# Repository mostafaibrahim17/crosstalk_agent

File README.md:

# Explainable Crosstalk Diagnosis on Arango

> A signal-integrity agent that finds the physical adjacency behind a board defect, ranks it,
> and cites how it was fixed before, as one query over one multimodel store.

<p align="center">
  <em>A board defect is not a value in one table. It is a relationship between two nets.</em>
</p>

When a data lane shows frequency variation and a rising bit error rate, every trace passes its
own design-rule check and the board still fails. The fault is not in any single net. It is a
**power or clock line running too close to a data line**, over a long enough parallel run to
couple noise into it. That proximity is an **edge, not a row**, which is exactly why
record-by-record inspection misses it.

This build models the board as a graph, gives that graph a memory of past defects, and resolves
both in a single [AQL](https://docs.arango.ai/arangodb/stable/aql/) query on the
[Arango Contextual Data Platform](https://arango.ai/products/contextual-data-platform).

---

## Architecture

One store holds three data shapes, and one query path turns a symptom into an explainable,
cited cause:

- **Design graph** - the KiCad board parsed into nets (nodes) and adjacency edges carrying
  spacing, parallel length, layer, and trace width.
- **Vector store** - past defect reports embedded for similarity recall via `APPROX_NEAR_COSINE`.
- **Knowledge graph** - built by [AutoGraph](https://docs.arango.ai/agentic-ai-suite/autograph/)
  from the same corpus, cited through the
  [GraphRAG Retriever](https://docs.arango.ai/agentic-ai-suite/graphrag/).

The agent recalls similar defects, traverses to the physical neighbors, **scores** each
candidate, **judges** which one explains the symptom, and returns a **cited fix**. The graph
proves the geometry; the agent interprets the cause.

---

## The hero fault

Point the engine at a real Raspberry Pi CM4 IO board with `python src/agent.py auto`. It scans
every adjacency, scores each one, and diagnoses the worst, with no victim hardcoded:

```
=== VICTIM ===
DSI1_D0_N (net_47)  symptom: frequency variation and rising bit error rate

=== CANDIDATES (ranked, proved) ===
  DSI0_C_P   sev 0.5873  [leading]    clock   gap 0.42mm  len 43.3mm  B.Cu
  DSI0_C_N   sev 0.4487  [unlikely]   clock   gap 0.80mm  len 43.3mm  B.Cu

=== RECALLED CASES ===
  Frequency variation traced to an impedance mismatch      <- same symptom, wrong cause
  Camera lane jitter from an adjacent high-speed signal
  Clock-to-data coupling over a long adjacent run

=== JUDGE (interpretation, a hypothesis) ===
  chosen: DSI0_C_P
  judge confidence: medium  ->  finding tier [corroborated]
  reasoning: DSI0_C_P runs on the same outer copper for 43.3 mm at 0.42 mm, a clock
  whose fast edges couple into a neighbouring data lane, matching the symptom.

=== CITED FIX (retriever) ===
  Increase local spacing; add a grounded guard trace with stitching vias; or reroute
  the aggressor to an inner layer. [cites the clock-coupling reports]

=== CORROBORATION ===
  mechanism converged : True
  verdict             : AGREE - graph and citation point at the same story
```

A DSI clock lane running 43 mm alongside a data lane from a *different* camera interface, 0.42 mm
apart on the bottom layer. The top vector match ("impedance mismatch") is the **wrong** cause,
sharing the symptom but not the geometry, and the graph corrects it.

---

## Why this architecture

The finding rests on **two independent surfaces agreeing**. The graph-and-judge chose the clock
coupling from geometry and reasoning. The Retriever, reading only the chosen cause, cited past
reports about the same mechanism from the knowledge graph. Neither was told the other's answer,
and they converged.

That convergence is the payoff of one multimodel store. A split stack, a graph database beside
a vector database, runs two queries, holds partial results in application code, and rebuilds the
join that finds the fault on every request. A vector-only tool has no topology to traverse and
cannot tell a real adjacency from a look-alike report. Two different shapes of the same store,
reaching the same mechanism independently, is the confidence a fragmented stack has no way to
reach.

The severity score weighs spacing and parallel length equally, because crosstalk accumulates
along a coupled run. The hero scores **high on length and loudness, low on spacing**, the exact
profile a proximity-only check misses.

---

## Quickstart

```bash
# clone and enter
git clone <your-repo-url> crosstalk-agent
cd crosstalk-agent

# virtual environment
python -m venv venv
source venv/bin/activate            # Windows: venv\Scripts\activate

# dependencies
pip install -r requirements.txt

# credentials
cp .env.example .env                # then edit with your details
```

```
# .env
ARANGO_HOST=https://<your-deployment>.arangodb.cloud
ARANGO_DB=crosstalk_v1
ARANGO_USER=root
ARANGO_PASSWORD=<your-password>
OPENAI_API_KEY=<your-key>
RETRIEVER_ID=                       # set after deploying the Retriever
RETRIEVER_BASE=
```

Build the data and run the diagnosis:

```bash
python src/prepare_autograph.py     # 1. write the synthetic defect corpus (30 reports)
python src/ingest.py                # 2. parse the board, load graph + vectors + index
python src/agent.py auto            # 3. scan the board, diagnose the worst adjacency
python src/agent.py auto --deep     # 3b. same, with Deep Search for a fuller cited playbook
```

**Step 2** reports `{'nets': 73, 'adjacencies': 10, 'defect_reports': 30, 'dimension': 1536}`.
Of 75 candidate net pairs, 65 are intended routing (differential pairs and same-interface buses)
and are skipped; the 10 that remain are the real cross-interface adjacencies.

To enable cited fixes, upload `data/autograph/*.md` to **AutoGraph Studio** in the Arango web
interface, build the graph with `text-embedding-3-small`, deploy the Retriever, and set
`RETRIEVER_ID` / `RETRIEVER_BASE`. The step-by-step walkthrough is in
[docs/setting-up-autograph-and-the-retriever.md](docs/setting-up-autograph-and-the-retriever.md).
Without it, the agent falls back to a local corpus citation and the rest of the pipeline runs
unchanged.

---

## The notebook

`crosstalk_analysis.ipynb` runs the whole pipeline end to end, cell by cell, from a fresh
database to the final figures. It closes with five visuals, all saved to `assets/`:

| figure | what it shows |
|---|---|
|  | every real adjacency, colored by class, sized by severity |
|  | the ten adjacencies ranked; the hero clears the field |
|  | spacing / length / loudness per candidate |
|  | spacing vs parallel length, with the 3W danger line |

---

## Repository layout

```
src/
  config.py             every knob: net classes, the 3W rule, severity weights, tiers
  parse_board.py        KiCad board -> nets and adjacency edges (skips intended routing)
  ingest.py             load the graph, embed the corpus, build the vector index
  prepare_autograph.py  generate the synthetic defect corpus for AutoGraph
  agent.py              the resolver: recall, traverse, score, judge, cite, corroborate
  agent_graph.py        the same investigation, driven by a LangGraph ReAct agent
data/
  CM4IOUSB3.kicad_pcb   the board
  autograph/            the generated corpus (markdown + manifest.json)
docs/
  setting-up-autograph-and-the-retriever.md   AutoGraph + Retriever provisioning walkthrough
assets/                 architecture diagram + figures saved by the notebook
crosstalk_analysis.ipynb
```

Every knob the engine turns lives in `config.py`. Swap your own process design kit's spacing
rule into the 3W threshold, point the parser at your board, and the ranking retunes with no
edit to any query.

---

## Two agents, one engine

The resolver in `agent.py` decides the step order itself. `agent_graph.py` hands the same three
tools (`traverse_and_score`, `recall_similar`, `cite_fix`) to a LangGraph ReAct agent that
chooses the order. Same tools, same database, same answer: the engine is the data and the query,
not the orchestration around it.

---

## Honest edges

The engine only catches faults that can be modeled as a relationship between nets; a defect that
is not an adjacency is invisible to it. The adjacency edges depend on a proximity threshold
someone chose. The top cause is a lead, not a verdict, capped at `corroborated` until confirmed
on silicon. The board is real geometry; the defect corpus is synthetic and labeled as such, so
the build demonstrates the method rather than real hardware history.

The same traversal extends to impedance mismatch, return-path discontinuity, and power-integrity
issues, because each is a relationship in the same graph. Run it earlier and it becomes a
design-rule check: the parser reads a layout in progress and flags an adjacency the day it is
routed, before any board is fabricated.

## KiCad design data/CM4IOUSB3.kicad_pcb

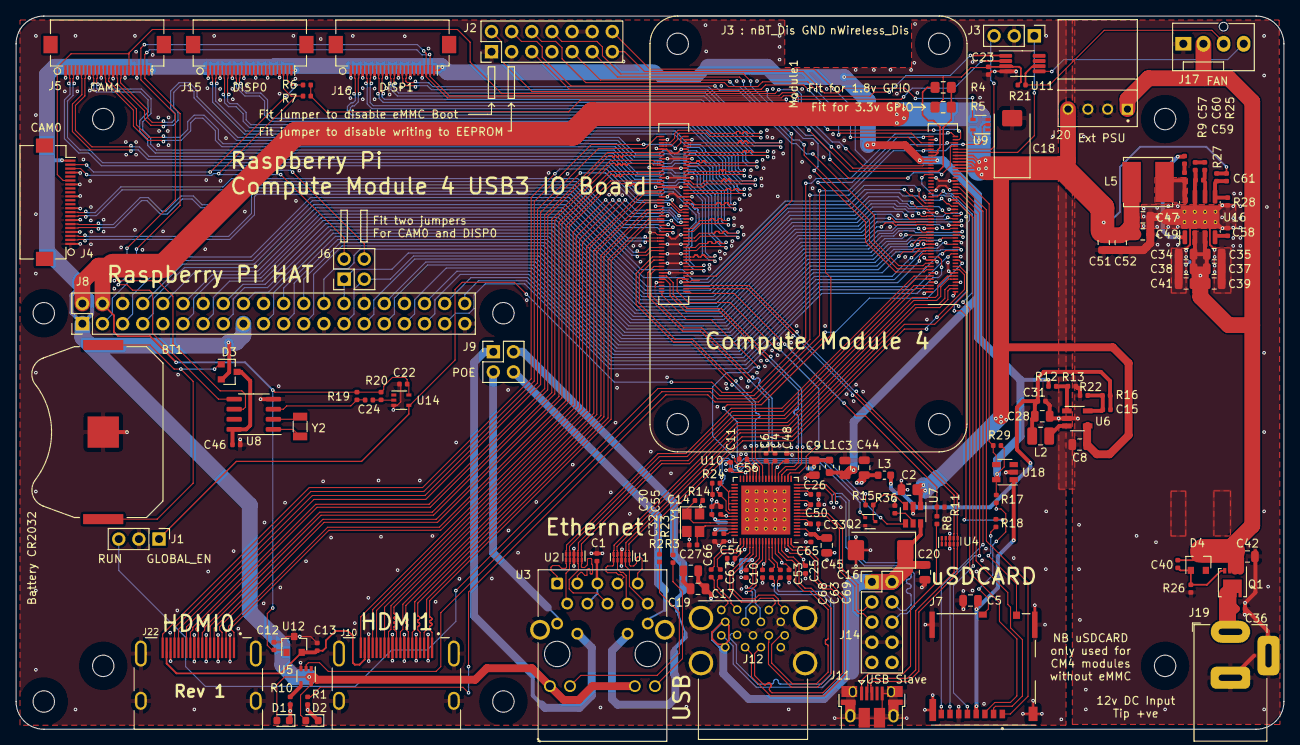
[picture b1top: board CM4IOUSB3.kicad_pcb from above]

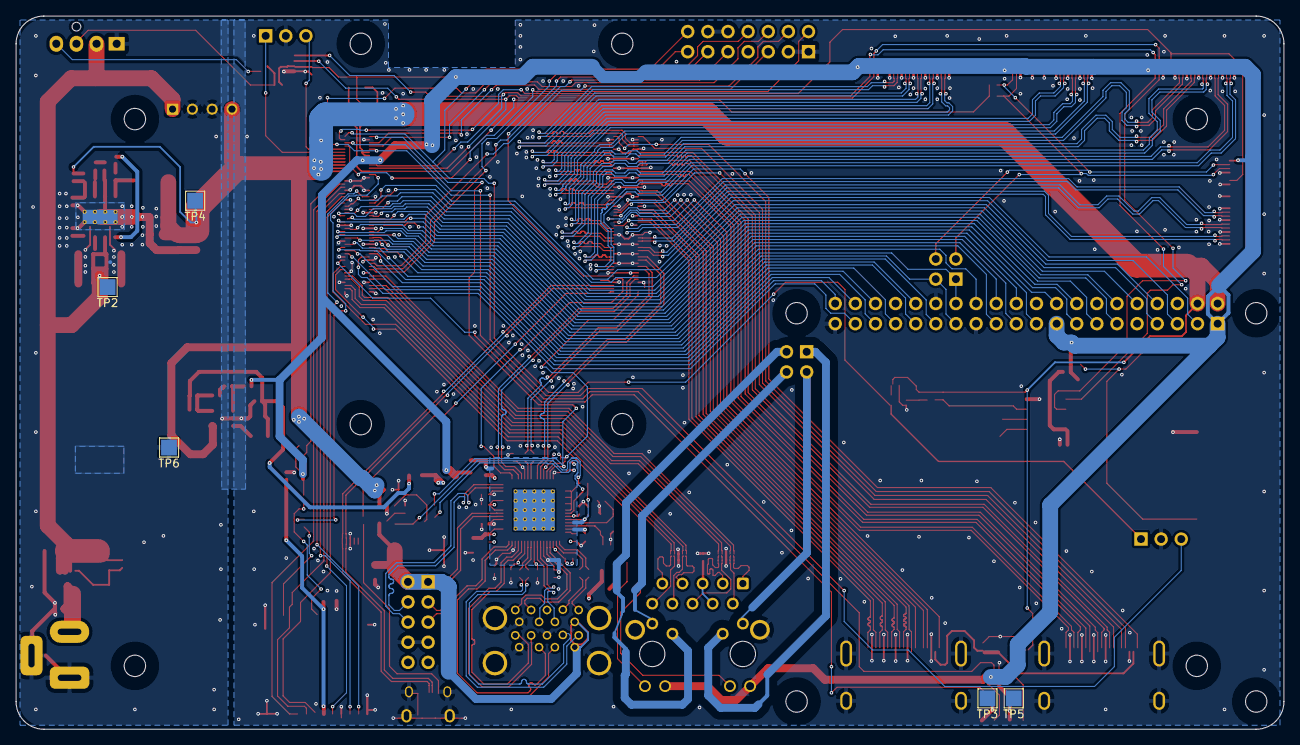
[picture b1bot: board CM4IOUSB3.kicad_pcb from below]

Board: 4 copper layers, 160.0 x 90.0 mm, 154 parts (5 on the bottom side), 209 nets.

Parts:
BT1: Battery_Cell; BatteryHolder_Keystone_3034_1x20mm
C1, C4, C6, C10, C11, C12, C13, C22, C23, C24, C25, C26, C30, C31, C32, C33, C40, C46, C48, C50, C53, C54, C55, C56, C57, C58, C63, C65, C66, C67, C68, C69: 100n; C_0402_1005Metric
C2, C3, C5, C8, C9, C17, C19, C20, C28, C44, C45, C47, C49, C51, C52: 10u; C_0805_2012Metric
C14, C15, C27: 22pF; C_0402_1005Metric
C16, C18: 100uF; CP_EIA-7343-31_Kemet-D
C34, C35, C37, C38, C39, C41, C42: 10u 35v; C_0805_2012Metric
C36: 100n 100v; C_0402_1005Metric
C59, C61: nf; C_0402_1005Metric
C60: 1.2nF; C_0402_1005Metric
D1: LED Red; LED_0603_1608Metric
D2: LED Green; LED_0603_1608Metric
D3: BAT54C-7-F; SOT-23
D4: MMBZ5242BLT3G; D_SOT-23_ANK
H1, H2, H3, H4, H5, H6, H7, H8: MountingHole; MountingHole_2.7mm_M2.5
J1, J3: Conn_01x03; PinHeader_1x03_P2.54mm_Vertical
J2: Conn_02x07_Odd_Even; PinHeader_2x07_P2.54mm_Vertical
J4, J5, J15, J16: Conn_01x22_Female; Hirose_FH12-22S-0.5SH_1x22-1MP_P0.50mm_Horizontal
J6, J9: THD-02-R; PinHeader_2x02_P2.54mm_Vertical
J7: Micro_SD_Card_Det; SDCARD_MOLEX_503398-1892
J8: THD-20-R; PinHeader_2x20_P2.54mm_Vertical
J10, J22: 690-019-298-412; EDAC 690-019-298-412
J11: USB_OTG; USB_Micro-B_EDAC_UCON00686
J12: USB3_A; MTCONN_UBAF30-D2011
J14: Conn_02x05_Odd_Even; PinHeader_2x05_P2.54mm_Vertical
J17: Molex 470531000; FanPinHeader_1x04_P2.54mm_Vertical
J19: Barrel_Jack; BarrelJack_Horizontal
J20: AMP171826-4; TE_171826-4
L1, L3: BLM18AG221SN1; L_0603_1608Metric
L2: 2.2uH; L_1008_2520Metric
L5: SRN6045TA-3R3Y; L_Bourns_SRN6045TA
Module1: ComputeModule4; Raspberry-Pi-4-Compute-Module
Q1: DMP3013SFV-7; Diodes_PowerDI3333-8
Q2: DMG1012T; SOT-523
R1, R10: 1k; R_0402_1005Metric
R2, R3: 470R; R_0402_1005Metric
R4: nf; R_0805_2012Metric_Pad1.15x1.40mm_HandSolder
R5: 0R; R_0805_2012Metric_Pad1.15x1.40mm_HandSolder
R6, R7, R8, R11, R28: 2.2K 1%; R_0402_1005Metric
R9: 10R; R_0402_1005Metric
R12, R13, R14, R15, R24, R36: 15K 1%; R_0402_1005Metric
R16, R26, R27, R29: 12K 1%; R_0402_1005Metric
R17, R18: nf; R_0402_1005Metric
R19, R20: 510K 1%; R_0402_1005Metric
R21: 36K 1%; R_0402_1005Metric
R22: 16K; R_0402_1005Metric
R23: 6.04K; R_0402_1005Metric
R25: 20K 1%; R_0402_1005Metric
TP2, TP3, TP4, TP5, TP6: TestPoint; TestPoint_Pad_2.0x2.0mm
U1, U2, U4: TPD4EUSB30; USON-10_2.5x1.0mm_P0.5mm
U3: MagJack-A70-112-331N126; TRJG0926HENL
U5, U9, U14: 74LVC1G07SE-7; SOT-353_SC-70-5
U6: AP3429KTTR-G1; TSOT-23-5
U7: AP22653W6; SOT-23-6
U8: PCF85063AT/AAZ; SOIC-8_3.9x4.9mm_P1.27mm
U10: VL805; QFN-68-1EP_8x8mm_P0.4mm_EP5.2x5.2mm_ThermalVias
U11: EMC2301-1-ACZL-TR; MSOP-8_3x3mm_P0.65mm
U12: RT9742SNGV; SOT-23
U16: AP64501SP-13; SOIC-8-1EP_3.9x4.9mm_P1.27mm_EP2.95x4.9mm_Mask2.71x3.4mm_Th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
U18: RT9742GGJ5; SOT-23-5
Y1: 25MHz; Crystal_SMD_SeikoEpson_FA238-4Pin_3.2x2.5mm
Y2: X32K768S301; Crystal_SMD_3215-2Pin_3.2x1.5mm

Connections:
/+3.3v: C3.1, C23.1, D1.2 (A), D2.2 (A), D3.2, J4.22, J5.22, J8.1, J8.17, J15.22, J16.22, L1.1, Module1.84 (+3.3v_(Output)), Module1.86 (+3.3v_(Output)), R5.1, R12.1, R17.1, R21.2, R29.1, U3.15 (LEDG_A), U3.17 (LEDY_A), U5.5 (VCC), U11.3 (VDD), U18.5 (IN)
/+5v: C2.1, C8.1, C12.1, C18.1, C22.1, C47.1, C49.1, C51.1, C52.1, C61.1, J8.2, J8.4, J20.4, L5.2, Module1.77 (+5v_(Input)), Module1.79 (+5v_(Input)), Module1.81 (+5v_(Input)), Module1.83 (+5v_(Input)), Module1.85 (+5v_(Input)), Module1.87 (+5v_(Input)), R19.2, R20.2, R27.1, TP4.1, U6.4 (VIN), U7.1 (IN), U9.5 (VCC), U12.1 (IN), U14.5 (VCC)
/+12v: C34.1, C35.1, C37.1, C38.1, C39.1, C40.1, C41.1, C42.1, D4.1 (K), J17.2, J20.1, Q1.1 (S), Q1.2 (S), Q1.3 (S), TP2.1, U16.2 (VIN), U16.3 (EN)
/CM4_GPIO ( Ethernet, GPIO, SDCARD)/+1.8v: Module1.88 (+1.8v_(Output)), Module1.90 (+1.8v_(Output)), R4.1
/CM4_GPIO ( Ethernet, GPIO, SDCARD)/AIN0: J2.5, Module1.96 (AnalogIP0)
/CM4_GPIO ( Ethernet, GPIO, SDCARD)/AIN1: J2.6, Module1.94 (AnalogIP1)
/CM4_GPIO ( Ethernet, GPIO, SDCARD)/BT_nDis: J3.3, Module1.91 (BT_nDisable)
/CM4_GPIO ( Ethernet, GPIO, SDCARD)/EEPROM_nWP: J2.4, Module1.20 (EEPROM_nWP)
/CM4_GPIO ( Ethernet, GPIO, SDCARD)/ETH_LEDG: Module1.17 (Ethernet_nLED2(3.3v)), R2.2
/CM4_GPIO ( Ethernet, GPIO, SDCARD)/ETH_LEDY: Module1.15 (Ethernet_nLED3(3.3v)), R3.2
/CM4_GPIO ( Ethernet, GPIO, SDCARD)/GLOBAL_EN: J1.1, J2.14, Module1.99 (Global_EN), U14.4
/CM4_GPIO ( Ethernet, GPIO, SDCARD)/GPIO2: J8.3, Module1.58 (GPIO2)
/CM4_GPIO ( Ethernet, GPIO, SDCARD)/GPIO3: J8.5, Module1.56 (GPIO3)
/CM4_GPIO ( Ethernet, GPIO, SDCARD)/GPIO4: J8.7, Module1.54 (GPIO4)
/CM4_GPIO ( Ethernet, GPIO, SDCARD)/GPIO5: J8.29, Module1.34 (GPIO5)
/CM4_GPIO ( Ethernet, GPIO, SDCARD)/GPIO6: J8.31, Module1.30 (GPIO6)
/CM4_GPIO ( Ethernet, GPIO, SDCARD)/GPIO7: J8.26, Module1.37 (GPIO7)
/CM4_GPIO ( Ethernet, GPIO, SDCARD)/GPIO8: J8.24, Module1.39 (GPIO8)
/CM4_GPIO ( Ethernet, GPIO, SDCARD)/GPIO9: J8.21, Module1.40 (GPIO9)
/CM4_GPIO ( Ethernet, GPIO, SDCARD)/GPIO10: J8.19, Module1.44 (GPIO10)
/CM4_GPIO ( Ethernet, GPIO, SDCARD)/GPIO11: J8.23, Module1.38 (GPIO11)
/CM4_GPIO ( Ethernet, GPIO, SDCARD)/GPIO12: J8.32, Module1.31 (GPIO12)
/CM4_GPIO ( Ethernet, GPIO, SDCARD)/GPIO13: J8.33, Module1.28 (GPIO13)
/CM4_GPIO ( Ethernet, GPIO, SDCARD)/GPIO14: J8.8, Module1.55 (GPIO14)
/CM4_GPIO ( Ethernet, GPIO, SDCARD)/GPIO15: J8.10, Module1.51 (GPIO15)
/CM4_GPIO ( Ethernet, GPIO, SDCARD)/GPIO16: J8.36, Module1.29 (GPIO16)
/CM4_GPIO ( Ethernet, GPIO, SDCARD)/GPIO17: J8.11, Module1.50 (GPIO17)
/CM4_GPIO ( Ethernet, GPIO, SDCARD)/GPIO18: J8.12, Module1.49 (GPIO18)
/CM4_GPIO ( Ethernet, GPIO, SDCARD)/GPIO19: J8.35, Module1.26 (GPIO19)
/CM4_GPIO ( Ethernet, GPIO, SDCARD)/GPIO20: J8.38, Module1.27 (GPIO20)
/CM4_GPIO ( Ethernet, GPIO, SDCARD)/GPIO21: J8.40, Module1.25 (GPIO21)
/CM4_GPIO ( Ethernet, GPIO, SDCARD)/GPIO22: J8.15, Module1.46 (GPIO22)
/CM4_GPIO ( Ethernet, GPIO, SDCARD)/GPIO23: J8.16, Module1.47 (GPIO23)
/CM4_GPIO ( Ethernet, GPIO, SDCARD)/GPIO24: J8.18, Module1.45 (GPIO24)
/CM4_GPIO ( Ethernet, GPIO, SDCARD)/GPIO25: J8.22, Module1.41 (GPIO25)
/CM4_GPIO ( Ethernet, GPIO, SDCARD)/GPIO26: J8.37, Module1.24 (GPIO26)
/CM4_GPIO ( Ethernet, GPIO, SDCARD)/GPIO27: J8.13, Module1.48 (GPIO27)
/CM4_GPIO ( Ethernet, GPIO, SDCARD)/GPIO_VREF: Module1.78 (GPIO_VREF(1.8v/3.3v_Input)), R4.2, R5.2, R6.1, R7.1
/CM4_GPIO ( Ethernet, GPIO, SDCARD)/ID_SC: J6.1, J8.28, Module1.35 (ID_SC)
/CM4_GPIO ( Ethernet, GPIO, SDCARD)/ID_SD: J6.3, J8.27, Module1.36 (ID_SD)
/CM4_GPIO ( Ethernet, GPIO, SDCARD)/RUN_PG: J1.3, Module1.92 (RUN_PG), U9.2
/CM4_GPIO ( Ethernet, GPIO, SDCARD)/Reserved: Module1.76 (Reserved), R18.1
/CM4_GPIO ( Ethernet, GPIO, SDCARD)/SD_CLK: J7.5 (CLK), Module1.57 (SD_CLK)
/CM4_GPIO ( Ethernet, GPIO, SDCARD)/SD_CMD: J7.3 (CMD), Module1.62 (SD_CMD)
/CM4_GPIO ( Ethernet, GPIO, SDCARD)/SD_DAT0: J7.7 (DAT0), Module1.63 (SD_DAT0)
/CM4_GPIO ( Ethernet, GPIO, SDCARD)/SD_DAT1: J7.8 (DAT1), Module1.67 (SD_DAT1)
/CM4_GPIO ( Ethernet, GPIO, SDCARD)/SD_DAT2: J7.1 (DAT2), Module1.69 (SD_DAT2)
/CM4_GPIO ( Ethernet, GPIO, SDCARD)/SD_DAT3: J7.2 (DAT3/CD), Module1.61 (SD_DAT3)
/CM4_GPIO ( Ethernet, GPIO, SDCARD)/SD_PWR: C5.1, J7.4 (VDD), U18.1 (OUT)
/CM4_GPIO ( Ethernet, GPIO, SDCARD)/SD_PWR_ON: Module1.75 (SD_PWR_ON), R29.2, U18.4 (EN)
/CM4_GPIO ( Ethernet, GPIO, SDCARD)/SYNC_IN: J2.8, Module1.16 (Ethernet_SYNC_IN(1.8v))
/CM4_GPIO ( Ethernet, GPIO, SDCARD)/SYNC_OUT: J2.9, Module1.18 (Ethernet_SYNC_OUT(1.8v))
/CM4_GPIO ( Ethernet, GPIO, SDCARD)/TR0_TAP: J9.3, U3.11 (VC1)
/CM4_GPIO ( Ethernet, GPIO, SDCARD)/TR1_TAP: J9.1, U3.12 (VC2)
/CM4_GPIO ( Ethernet, GPIO, SDCARD)/TR2_TAP: J9.2, U3.13 (VC3)
/CM4_GPIO ( Ethernet, GPIO, SDCARD)/TR3_TAP: J9.4, U3.14 (VC4)
/CM4_GPIO ( Ethernet, GPIO, SDCARD)/TRD0_N: Module1.10 (Ethernet_Pair0_N), U2.4 (D2+), U2.7, U3.2 (TRD0-)
/CM4_GPIO ( Ethernet, GPIO, SDCARD)/TRD0_P: Module1.12 (Ethernet_Pair0_P), U2.5 (D2-), U2.6, U3.1 (TRD0+)
/CM4_GPIO ( Ethernet, GPIO, SDCARD)/TRD1_N: Module1.6 (Ethernet_Pair1_N), U2.2 (D1-), U2.9, U3.6 (TRD1-)
/CM4_GPIO ( Ethernet, GPIO, SDCARD)/TRD1_P: Module1.4 (Ethernet_Pair1_P), U2.1 (D1+), U2.10, U3.3 (TRD1+)
/CM4_GPIO ( Ethernet, GPIO, SDCARD)/TRD2_N: Module1.9 (Ethernet_Pair2_N), U1.4 (D2+), U1.7, U3.8 (TRD2-)
/CM4_GPIO ( Ethernet, GPIO, SDCARD)/TRD2_P: Module1.11 (Ethernet_Pair2_P), U1.5 (D2-), U1.6, U3.7 (TRD2+)
/CM4_GPIO ( Ethernet, GPIO, SDCARD)/TRD3_N: Module1.5 (Ethernet_Pair3_N), U1.2 (D1-), U1.9, U3.10 (TRD3-)
/CM4_GPIO ( Ethernet, GPIO, SDCARD)/TRD3_P: Module1.3 (Ethernet_Pair3_P), U1.1 (D1+), U1.10, U3.9 (TRD3+)
/CM4_GPIO ( Ethernet, GPIO, SDCARD)/TV_OUT: J2.11, Module1.111 (VDAC_COMP)
/CM4_GPIO ( Ethernet, GPIO, SDCARD)/WL_nDis: J3.1, Module1.89 (WL_nDisable)
/CM4_GPIO ( Ethernet, GPIO, SDCARD)/nPWR_LED: Module1.95 (nPI_LED_PWR), U5.2
/CM4_GPIO ( Ethernet, GPIO, SDCARD)/nRPIBOOT: J2.2, Module1.93 (nRPIBOOT)
/CM4_HighSpeed/CAM0_C_N: J4.8, Module1.140 (CAM0_C_N)
/CM4_HighSpeed/CAM0_C_P: J4.9, Module1.142 (CAM0_C_P)
/CM4_HighSpeed/CAM0_D0_N: J4.2, Module1.128 (CAM0_D0_N)
/CM4_HighSpeed/CAM0_D0_P: J4.3, Module1.130 (CAM0_D0_P)
/CM4_HighSpeed/CAM0_D1_N: J4.5, Module1.134 (CAM0_D1_N)
/CM4_HighSpeed/CAM0_D1_P: J4.6, Module1.136 (CAM0_D1_P)
/CM4_HighSpeed/CAM1_C_N: J5.8, Module1.127 (CAM1_C_N)
/CM4_HighSpeed/CAM1_C_P: J5.9, Module1.129 (CAM1_C_P)
/CM4_HighSpeed/CAM1_D0_N: J5.2, Module1.115 (CAM1_D0_N)
/CM4_HighSpeed/CAM1_D0_P: J5.3, Module1.117 (CAM1_D0_P)
/CM4_HighSpeed/CAM1_D1_N: J5.5, Module1.121 (CAM1_D1_N)
/CM4_HighSpeed/CAM1_D1_P: J5.6, Module1.123 (CAM1_D1_P)
/CM4_HighSpeed/CAM1_D2_N: J5.11, Module1.133 (CAM1_D2_N)
/CM4_HighSpeed/CAM1_D2_P: J5.12, Module1.135 (CAM1_D2_P)
/CM4_HighSpeed/CAM1_D3_N: J5.14, Module1.139 (CAM1_D3_N)
/CM4_HighSpeed/CAM1_D3_P: J5.15, Module1.141 (CAM1_D3_P)
/CM4_HighSpeed/CAM_GPIO: J4.17, J5.17, Module1.97 (Camera_GPIO)
/CM4_HighSpeed/DSI0_C_N: J15.8, Module1.169 (DSI0_C_N)
/CM4_HighSpeed/DSI0_C_P: J15.9, Module1.171 (DSI0_C_P)
/CM4_HighSpeed/DSI0_D0_N: J15.2, Module1.157 (DSI0_D0_N)
/CM4_HighSpeed/DSI0_D0_P: J15.3, Module1.159 (DSI0_D0_P)
/CM4_HighSpeed/DSI0_D1_N: J15.5, Module1.163 (DSI0_D1_N)
/CM4_HighSpeed/DSI0_D1_P: J15.6, Module1.165 (DSI0_D1_P)
/CM4_HighSpeed/DSI1_C_N: J16.8, Module1.187 (DSI1_C_N)
/CM4_HighSpeed/DSI1_C_P: J16.9, Module1.189 (DSI1_C_P)
/CM4_HighSpeed/DSI1_D0_N: J16.2, Module1.175 (DSI1_D0_N)
/CM4_HighSpeed/DSI1_D0_P: J16.3, Module1.177 (DSI1_D0_P)
/CM4_HighSpeed/DSI1_D1_N: J16.5, Module1.181 (DSI1_D1_N)
/CM4_HighSpeed/DSI1_D1_P: J16.6, Module1.183 (DSI1_D1_P)
/CM4_HighSpeed/DSI1_D2_N: J16.11, Module1.193 (DSI1_D2_N)
/CM4_HighSpeed/DSI1_D2_P: J16.12, Module1.195 (DSI1_D2_P)
/CM4_HighSpeed/DSI1_D3_N: J16.14, Module1.194 (DSI1_D3_N)
/CM4_HighSpeed/DSI1_D3_P: J16.15, Module1.196 (DSI1_D3_P)
/CM4_HighSpeed/HDMI0_CEC: J22.13 (CEC), Module1.151 (HDMI0_CEC)
/CM4_HighSpeed/HDMI0_CK_N: J22.12 (CK-), Module1.190 (HDMI0_CLK_N)
/CM4_HighSpeed/HDMI0_CK_P: J22.10 (CK+), Module1.188 (HDMI0_CLK_P)
/CM4_HighSpeed/HDMI0_D0_N: J22.9 (D0-), Module1.184 (HDMI0_TX0_N)
/CM4_HighSpeed/HDMI0_D0_P: J22.7 (D0+), Module1.182 (HDMI0_TX0_P)
/CM4_HighSpeed/HDMI0_D1_N: J22.6 (D1-), Module1.178 (HDMI0_TX1_N)
/CM4_HighSpeed/HDMI0_D1_P: J22.4 (D1+), Module1.176 (HDMI0_TX1_P)
/CM4_HighSpeed/HDMI0_D2_N: J22.3 (D2-), Module1.172 (HDMI0_TX2_N)
/CM4_HighSpeed/HDMI0_D2_P: J22.1 (D2+), Module1.170 (HDMI0_TX2_P)
/CM4_HighSpeed/HDMI0_HOTPLUG: J22.19 (HPD/HEAC-), Module1.153 (HDMI0_HOTPLUG)
/CM4_HighSpeed/HDMI0_SCL: J22.15 (SCL), Module1.200 (HDMI0_SCL)
/CM4_HighSpeed/HDMI0_SDA: J22.16 (SDA), Module1.199 (HDMI0_SDA)
/CM4_HighSpeed/HDMI1_CEC: J10.13 (CEC), Module1.149 (HDMI1_CEC)
/CM4_HighSpeed/HDMI1_CK_N: J10.12 (CK-), Module1.166 (HDMI1_CLK_N)
/CM4_HighSpeed/HDMI1_CK_P: J10.10 (CK+), Module1.164 (HDMI1_CLK_P)
/CM4_HighSpeed/HDMI1_D0_N: J10.9 (D0-), Module1.160 (HDMI1_TX0_N)
/CM4_HighSpeed/HDMI1_D0_P: J10.7 (D0+), Module1.158 (HDMI1_TX0_P)
/CM4_HighSpeed/HDMI1_D1_N: J10.6 (D1-), Module1.154 (HDMI1_TX1_N)
/CM4_HighSpeed/HDMI1_D1_P: J10.4 (D1+), Module1.152 (HDMI1_TX1_P)
/CM4_HighSpeed/HDMI1_D2_N: J10.3 (D2-), Module1.148 (HDMI1_TX2_N)
/CM4_HighSpeed/HDMI1_D2_P: J10.1 (D2+), Module1.146 (HDMI1_TX2_P)
/CM4_HighSpeed/HDMI1_HOTPLUG: J10.19 (HPD/HEAC-), Module1.143 (HDMI1_HOTPLUG)
/CM4_HighSpeed/HDMI1_SCL: J10.15 (SCL), Module1.147 (HDMI1_SCL)
/CM4_HighSpeed/HDMI1_SDA: J10.16 (SDA), Module1.145 (HDMI1_SDA)
/CM4_HighSpeed/HDMI_5v: C13.1, J10.18 (+5V), J22.18 (+5V), U12.2 (OUT)
/CM4_HighSpeed/PCIE_CLK_N: Module1.112 (PCIe_CLK_N), U10.21 (PEXCLK_P)
/CM4_HighSpeed/PCIE_CLK_P: Module1.110 (PCIe_CLK_P), U10.22 (PEXCLK_N)
/CM4_HighSpeed/PCIE_CLK_nREQ: Module1.102 (PCIe_CLK_nREQ), U10.30 (nPEXCLKREQ)
/CM4_HighSpeed/PCIE_RX_N: C6.2, Module1.118 (PCIe_RX_N)
/CM4_HighSpeed/PCIE_RX_P: C4.2, Module1.116 (PCIe_RX_P)
/CM4_HighSpeed/PCIE_TX_N: Module1.124 (PCIe_TX_N), U10.28 (PEXRX_N)
/CM4_HighSpeed/PCIE_TX_P: Module1.122 (PCIe_TX_P), U10.27 (PEXRX_P)
/CM4_HighSpeed/PCIE_nRST: Module1.109 (PCIe_nRST), U10.19 (nPEXRST)
/CM4_HighSpeed/SCL0: J5.20, J16.20, Module1.80 (SCL0), U8.6 (SCL), U11.2 (SCL)
/CM4_HighSpeed/SCL1: J4.20, J6.2, J15.20, R7.2
/CM4_HighSpeed/SDA0: J5.21, J16.21, Module1.82 (SDA0), U8.5 (SDA), U11.1 (SDA)
/CM4_HighSpeed/SDA1: J4.21, J6.4, J15.21, R6.2
/CM4_HighSpeed/USBOTG_ID: Module1.101 (USB_OTG_ID), R8.2, R11.1
/RTC , Wakeup, FAN/nRTC_INT: C24.2, R19.1, U8.3 (~INT)
/USB2/USBD_N: J11.2 (D-), Module1.103 (USB2_N), U4.4 (D2+), U4.7
/USB2/USBD_P: J11.3 (D+), Module1.105 (USB2_P), U4.5 (D2-), U4.6
/nEXTRST: Module1.100 (nEXTRST), R15.1, U10.31 (nPONRST)
/xHCI-USB3/A1.05v: C44.1, C45.1, C50.1, C53.1, C54.1, C55.1, C56.1, C63.1, C65.1, L3.2, U10.3 (VCCA10SSRX34), U10.9 (VDD), U10.12 (VCCA10SSRX34), U10.29 (VDD), U10.45 (VDD), U10.54 (VCCA10SSRX12), U10.60 (VDD), U10.63 (VCCA10SSRX12)
/xHCI-USB3/A3.3v: C9.1, C10.1, C11.1, C25.1, C26.1, C30.1, C32.1, C33.1, C48.1, L1.2, R14.1, R24.1, U10.6 (VCCA33SS34), U10.15 (VCCA33SS34), U10.23 (VCCA33PEX), U10.32 (VSUS33), U10.46 (VSUS33), U10.49 (VCCA33SSM), U10.57 (VCCA33SS12), U10.66 (VCCA33SS12)
/xHCI-USB3/C1_N: C67.2, U10.53 (SSTX1_N)
/xHCI-USB3/C1_P: C66.2, U10.52 (SSTX1_P)
/xHCI-USB3/C2_N: C69.2, U10.62 (SSTX2_N)
/xHCI-USB3/C2_P: C68.2, U10.61 (SSTX2_P)
/xHCI-USB3/PD1_N: J12.B2 (D-), U10.59 (USB2D1_N)
/xHCI-USB3/PD1_P: J12.B3 (D+), U10.58 (USB2D1_P)
/xHCI-USB3/PD2_N: J12.A2 (D-), U10.68 (USB2D2_N)
/xHCI-USB3/PD2_P: J12.A3 (D+), U10.67 (USB2D2_P)
/xHCI-USB3/PD3_N: J14.3, U10.8 (USB2D3_N)
/xHCI-USB3/PD3_P: J14.5, U10.7 (USB2D3_P)
/xHCI-USB3/PD4_N: J14.4, U10.17 (USB2D4_N)
/xHCI-USB3/PD4_P: J14.6, U10.16 (USB2D4_P)
/xHCI-USB3/PEXTX_N: C6.1, U10.25 (PEXTX_N)
/xHCI-USB3/PEXTX_P: C4.1, U10.24 (PEXTX_P)
/xHCI-USB3/PWR: Q2.3 (D), R15.2, U7.3 (EN)
/xHCI-USB3/SSRX1_N: J12.B5 (SSRX-), U10.56 (SSRX1_N)
/xHCI-USB3/SSRX1_P: J12.B6 (SSRX+), U10.55 (SSRX1_P)
/xHCI-USB3/SSRX2_N: J12.A6 (SSRX+), U10.65 (SSRX2_N)
/xHCI-USB3/SSRX2_P: J12.A5 (SSRX-), U10.64 (SSRX2_P)
/xHCI-USB3/SSTX1_N: C67.1, J12.B8 (SSTX-)
/xHCI-USB3/SSTX1_P: C66.1, J12.B9 (SSTX+)
/xHCI-USB3/SSTX2_N: C69.1, J12.A9 (SSTX+)
/xHCI-USB3/SSTX2_P: C68.1, J12.A8 (SSTX-)
/xHCI-USB3/VBUS: C16.1, C17.1, C19.1, C20.1, J12.A1 (VBUS), J12.B1 (VBUS), J14.1, J14.2, U7.6 (OUT)
/xHCI-USB3/nOCS1: R24.2, U7.4 (nFault), U10.37 (nUSBHOC4), U10.39 (nUSBHOC3), U10.41 (nUSBHOC2), U10.43 (nUSBHOC1)
/xHCI-USB3/nPWR: Q2.1 (G), R14.2, U10.44 (nUSBHPE1)
GND: BT1.2 (-), C1.2, C2.2, C3.2, C5.2, C8.2, C9.2, C10.2, C11.2, C12.2, C13.2, C14.2, C16.2, C17.2, C18.2, C19.2, C20.2, C22.2, C23.2, C25.2, C26.2, C27.2, C28.2, C30.2, C31.2, C32.2, C33.2, C34.2, C35.2, C36.2, C37.2, C38.2, C39.2, C41.2, C42.2, C44.2, C45.2, C46.2, C47.2, C48.2, C49.2, C50.2, C51.2, C52.2, C53.2, C54.2, C55.2, C56.2, C58.2, C59.2, C60.2, C63.2, C65.2, J1.2, J2.1, J2.3, J2.7, J2.10, J2.12, J3.2, J4.1, J4.4, J4.7, J4.10, J4.13, J4.16, J4.19, J5.1, J5.4, J5.7, J5.10, J5.13, J5.16, J5.19, J7.6 (VSS), J7.11 (SHIELD), J8.6, J8.9, J8.14, J8.20, J8.25, J8.30, J8.34, J8.39, J10.2 (D2S), J10.5 (D1S), J10.8 (D0S), J10.11 (CKS), J10.17 (GND), J10.SH1 (SH), J10.SH2 (SH), J10.SH3 (SH), J10.SH4 (SH), J11.5 (GND), J11.6 (Shield), J12.10 (SHIELD), J12.A4 (GND), J12.A7 (DRAIN), J12.B4 (GND), J12.B7 (DRAIN), J14.7, J14.8, J15.1, J15.4, J15.7, J15.10, J15.13, J15.16, J15.19, J16.1, J16.4, J16.7, J16.10, J16.13, J16.16, J16.19, J17.1, J19.2, J19.3, J20.2, J20.3, J22.2 (D2S), J22.5 (D1S), J22.8 (D0S), J22.11 (CKS), J22.17 (GND), J22.SH1 (SH), J22.SH2 (SH), J22.SH3 (SH), J22.SH4 (SH), Module1.1 (GND), Module1.2 (GND), Module1.7 (GND), Module1.8 (GND), Module1.13 (GND), Module1.14 (GND), Module1.22 (GND), Module1.23 (GND), Module1.32 (GND), Module1.33 (GND), Module1.42 (GND), Module1.43 (GND), Module1.52 (GND), Module1.53 (GND), Module1.59 (GND), Module1.60 (GND), Module1.65 (GND), Module1.66 (GND), Module1.71 (GND), Module1.74 (GND), Module1.98 (GND), Module1.107 (GND), Module1.108 (GND), Module1.113 (GND), Module1.114 (GND), Module1.119 (GND), Module1.120 (GND), Module1.125 (GND), Module1.126 (GND), Module1.131 (GND), Module1.132 (GND), Module1.137 (GND), Module1.138 (GND), Module1.144 (GND), Module1.150 (GND), Module1.155 (GND), Module1.156 (GND), Module1.161 (GND), Module1.162 (GND), Module1.167 (GND), Module1.168 (GND), Module1.173 (GND), Module1.174 (GND), Module1.179 (GND), Module1.180 (GND), Module1.185 (GND), Module1.186 (GND), Module1.191 (GND), Module1.192 (GND), Module1.197 (GND), Module1.198 (GND), Q2.2 (S), R11.2, R13.2, R22.2, R23.2, R26.2, R28.2, R36.2, TP6.1, U1.3 (GND), U1.8 (GND), U2.3 (GND), U2.8 (GND), U3.19 (SHIELD), U3.20 (SHIELD), U4.3 (GND), U4.8 (GND), U5.3 (GND), U6.2 (GND), U7.2 (GND), U8.4 (VSS), U9.3 (GND), U10.69 (PAD_GND), U11.4 (GND), U12.3 (GND), U14.3 (GND), U16.7 (GND), U16.9 (EP), U18.2 (GND), Y1.2, Y1.4
unnamed: BT1.1 (+), D3.1
unnamed: C1.1, U3.4 (CT), U3.5 (CT)
unnamed: C14.1, U10.47 (SSXI), Y1.1
unnamed: C15.1, C28.1, C31.1, L2.2, L3.1, R16.1
unnamed: C15.2, R16.2, R22.1, U6.5 (FB)
unnamed: C24.1, R20.1, U14.2
unnamed: C27.1, U10.48 (SSX0), Y1.3
unnamed: C36.1, J19.1, Q1.5 (D)
unnamed: C40.2, D4.2 (A), Q1.4 (G), R26.1
unnamed: C46.1, D3.3, U8.8 (VDD)
unnamed: C57.1, R9.2
unnamed: C57.2, U16.1 (BST)
unnamed: C58.1, U16.4 (SS)
unnamed: C59.1, R25.1, U16.6 (COMP)
unnamed: C60.1, R25.2
unnamed: C61.2, R27.2, R28.1, U16.5 (FB)
unnamed: D1.1 (K), R10.1, TP5.1
unnamed: D2.1 (K), R1.1, TP3.1
unnamed: J2.13, U9.4
unnamed: J7.9 (DET_B), R18.2
unnamed: J7.10 (DET_A), R17.2
unnamed: J11.1 (VBUS), R8.1
unnamed: J17.3, R21.1, U11.6 (TACH)
unnamed: J17.4, U11.5 (PWM)
unnamed: L2.1, U6.3 (LX)
unnamed: L5.1, R9.1, U16.8 (SW)
unnamed: Module1.21 (PI_nLED_Activity), R1.2
unnamed: R2.1, U3.16 (LEDG_K)
unnamed: R3.1, U3.18 (LEDY_K)
unnamed: R10.2, U5.4
unnamed: R12.2, R13.1, U6.1 (EN)
unnamed: R23.1, U10.50 (SSREXT)
unnamed: R36.1, U7.5 (ILIM)
unnamed: U4.1 (D1+), U4.10
unnamed: U4.2 (D1-), U4.9
unnamed: U8.1 (OSCI), Y2.2
unnamed: U8.2 (OSCO), Y2.1
